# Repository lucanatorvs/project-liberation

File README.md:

# Project Liberation
Project Liberation is een weerstation welke doormiddel van een ESP-32 over WiFi
de meet-data naar het Britse meteorologisch instituut
([MetOffice](https://www.metoffice.gov.uk/)) communiceert zodat deze beschikbaar
worden in de [WOW-NL](https://wow.knmi.nl/) database van de KNMI.

## assembling
for assembling instructions pleas see the pdf at ./instructions/instructions.pdf

## flashing the esp
Use a 'USB to serial' programer and conect the pins: 3v3, GND, RXD, TXD, DTR and RTS. 
Remember that the RX on the programer sould go to the TX on the esp and so the pcb, and visversa.
In arduino, open the scetch and select the port of youre programer.
Install the esp32 boardmaniger by adding the url `https://dl.espressif.com/dl/package_esp32_index.json` to the "additional board maniger URLs" section in youre arduino settings.
A list of the drivers is given and if all the drivers are installed, you sould be able to flach the esp.

## Keeping our logs clean
Please read this and keep it in mind when writing commit messages:
[How to Write a Git Commit Message](https://chris.beams.io/posts/git-commit/)

Also, please put this in your `~/.gitconfig` (if you care why read 
[this](https://kalamuna.atlassian.net/wiki/display/KALA/Git+Workflow)):
```
[branch]
  autosetuprebase = always
[core]
  mergeoptions = --no-commit --no-ff
```

## Contibuting
Pull requests are welcome. For major changes, please open an issue first to discuss what you would like to change.

## Licence
[MIT](./LICENSE)

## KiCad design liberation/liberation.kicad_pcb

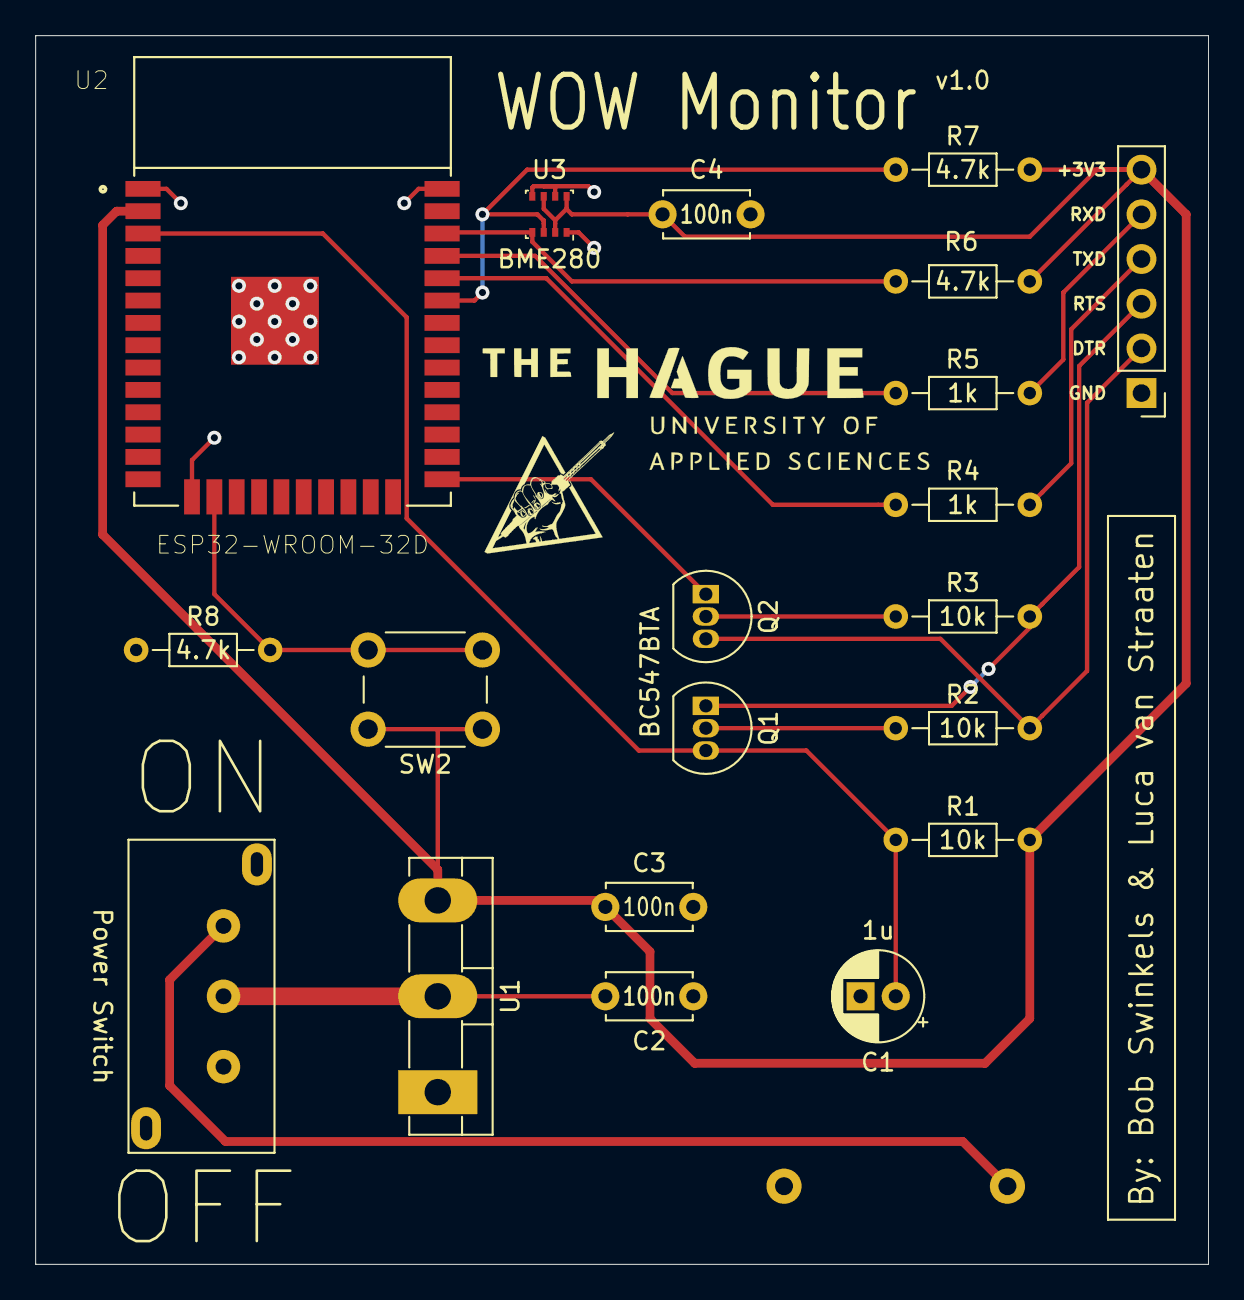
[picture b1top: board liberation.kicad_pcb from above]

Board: 2 copper layers, 66.7 x 69.8 mm, 21 parts (1 on the bottom side), 17 nets.

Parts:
BT1: Battery; keystone_2477
C1: 1u; CP_Radial_D5.0mm_P2.00mm
C2, C3, C4: 100n; C_Disc_D4.7mm_W2.5mm_P5.00mm
Jserial1: Hedd_01x06_Male; PinHeader_1x06_P2.54mm_Vertical
Q1, Q2: BC547BTA; TO-92_Inline
R1, R2, R3: 10k; R_Axial_DIN0204_L3.6mm_D1.6mm_P7.62mm_Horizontal
R4, R5: 1k; R_Axial_DIN0204_L3.6mm_D1.6mm_P7.62mm_Horizontal
R6, R7, R8: 4.7k; R_Axial_DIN0204_L3.6mm_D1.6mm_P7.62mm_Horizontal
SW1: MHS122K; MHS122
SW2: FSM4JAH; SW_PUSH_6mm_H5mm
U1: NJU7223F33
U2: ESP32-WROOM-32D; MODULE_ESP32-WROOM-32D
U3: BME280; Bosch_LGA-8_2.5x2.5mm_P0.65mm_ClockwisePinNumbering

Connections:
+3V3: C3.1, C4.2, Jserial1.6, R1.1, R6.1, R7.1, SW2.1, U1.3, U2.2, U3.2, U3.6, U3.8
BOOT: Q2.1, U2.25
DTR: Jserial1.2, Q2.3, R2.2
GND: BT1.2, C1.2, C2.2, C3.2, C4.1, Jserial1.1, R8.2, U1.2, U2.1, U2.15, U2.38, U2.39, U3.1, U3.5, U3.7
unnamed: BT1.1, SW1.1
unnamed: Q1.2, R2.1
unnamed: Q2.2, R3.1
unnamed: R4.1, U2.34
unnamed: R5.1, U2.35
RECONF: R8.1, SW2.2, U2.16
RESET: C1.1, Q1.3, R1.2, U2.3
RTS: Jserial1.3, Q1.1, R3.2
RXD: Jserial1.5, R5.2
SCL: R6.2, U2.36, U3.4
SDA: R7.2, U2.33, U3.3
TXD: Jserial1.4, R4.2
VBAT: C2.1, SW1.2, U1.1

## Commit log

2019-11-15 Initial commit, empty KiCad project
2019-11-15 Update README and add MIT license
2019-11-15 Fix link to LICENSE
2019-11-15 add kicad spesific .gitignore
2019-11-15 add scematic esp-wroom-32D and bme260
2019-11-16 making i2c conection and boot reset
2019-11-16 start flashing instructions
2019-11-18 finich the flashing instructions
2019-11-18 boost converter sircuit
2019-11-18 add liniar voltige regulator
2019-11-18 Add complete BOM
2019-11-18 schema en netlist af
2019-11-18 scheam af nu
2019-11-18 Update BOM and add bestelllijst
2019-11-18 pcs begin
2019-11-18 Make PCB design (almost) complete :p
2019-11-19 finich pcb and secmatic for ordering
2019-11-24 date titelblocks today
2019-11-24 date and titel block on pcb correct
2019-11-24 Revert "date titelblocks today"
    This reverts commit 034fccc4a2562568847e0a5f0e35f07e7201a5d0.
2019-11-25 start instructions for asembeling
2019-11-25 look at all the chicken
2019-11-25 set up instructions, no spelcheck
2019-11-26 finich instructions
2019-12-19 Add Arduino code
